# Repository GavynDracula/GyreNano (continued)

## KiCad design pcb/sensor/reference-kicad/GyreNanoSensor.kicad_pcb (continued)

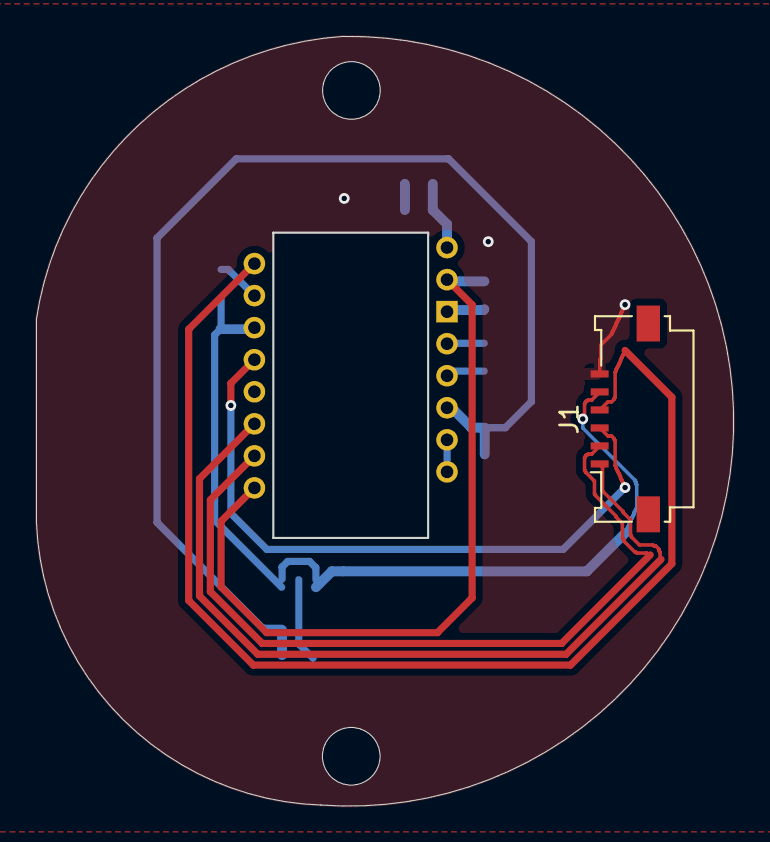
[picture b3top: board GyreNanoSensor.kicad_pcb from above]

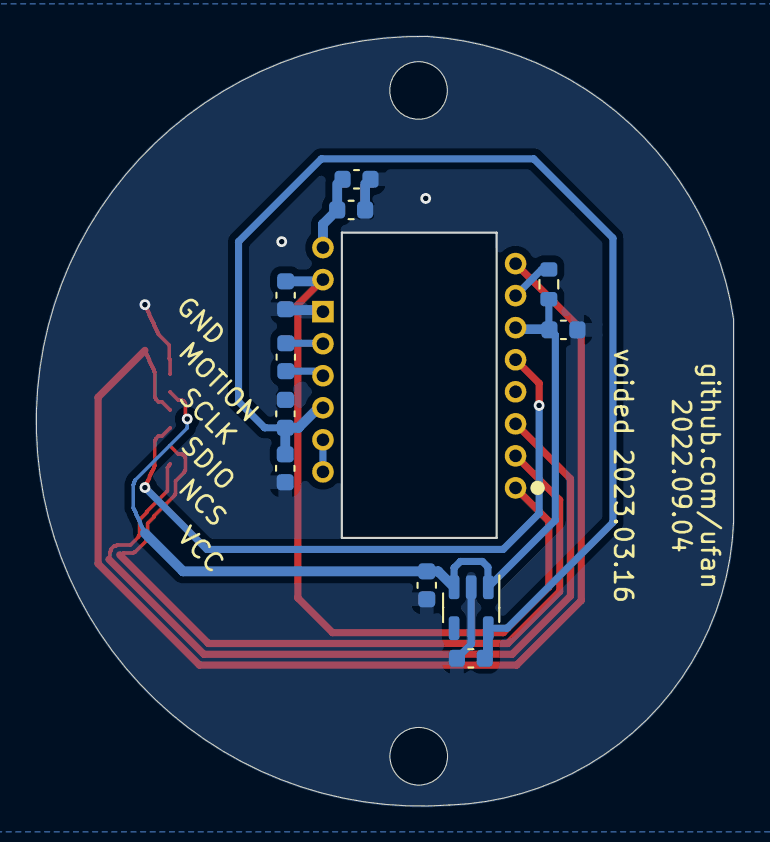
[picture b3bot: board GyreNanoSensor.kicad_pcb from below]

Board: 2 copper layers, 38.7 x 42.8 mm, 15 parts (12 on the bottom side), 13 nets.

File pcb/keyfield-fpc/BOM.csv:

采购类别,物料,型号或参数,封装规格,一套用量,建议备料数量,已有数量,还缺数量,说明
核心,MX热插拔座,Kailh CPG151101S11-16,MX socket,35,40,,,主列30+拇指5
核心,按键二极管,1N4148W-7-F,SOD-123,35,50或100,,,不得误买SOD-323
核心,FFC插座,Molex 2005280060,6P 1mm 下接触 卧贴,27,30,,,FPC12+holder14+sensor1；左J7可少装1；已焊件扣减
核心,电源开关,C&K JS102011SAQN,SPDT SMT,2,3,,,holder SW1
核心,电池板端插座,JST B2B-PH-SM4-TB,PH2.0 2P立式贴片,2,3,,,不是直插座
复用或采购,电池插头线,PHR-2配套线,PH2.0 2P,2,2或复用,,,板端1正2负；实测极性
待试装,FFC排线,6芯 1.00mm 插入端0.30±0.05mm,接点面及长度待定,13,先小样,,,12键区+1sensor；可试100/150/250mm同面异面各1，不是定长采购表
复用,主控,nrfmicro 1.4,现有模块,2,优先复用,,,替代主控需重新核对引脚电源和充电
待试装,主控排针,1x12 2.54mm,高度待确认,4,沿用或4条,,,可拔插还需4条匹配排母；未冻结堆叠
复用,轴体,现有MX兼容轴,MX,35,复用,,,
复用,键帽,现有键帽,匹配现用轴,35,复用,,,
复用,电池,现用电池,尺寸容量待记录,2,复用,,,
复用,球及光学组件,34mm球+原适配器镜片轴承,原组合,1,复用,,,
条件采购：新sensor,传感器,PMW3610,源板U2封装,1,1或复用,,,具体后缀和光学组合需核对；不买任意模块替代
条件采购：新sensor,LDO,TCR2EF19,SOT-25/SMV 1.9V,1,2,,,U1；不要混用1.8V版
条件采购：新sensor,电容 C1 C9,10nF X7R >=10V,0603/1608,2,10,,,采购候选参数；旧LCSC编号不用
条件采购：新sensor,电容 C2 C4 C6 C7,100nF X7R >=10V,0603/1608,4,10,,,C4本版100nF
条件采购：新sensor,电容 C3,3.3uF 16V X5R/X7R候选,0603/1608,1,10,,,核对有效容量和LDO要求
条件采购：新sensor,电容 C5,1uF X7R >=10V,0603/1608,1,10,,,
条件采购：新sensor,电容 C8,10uF X7R >=6.3V,0603/1608,1,10,,,具体MPN待选，核对直流偏压有效容量
条件采购：新sensor,电阻 R1,2Mohm 1%,0603/1608,1,10,,,
机械,无铜FR4背衬,0.40mm 按DXF,每键独立,35,做2套18件共36,,,右侧剩1件；可另备试验件
待验证,背衬胶,胶层预算0.05mm,型号未冻结,1,先小样,,,胶层耐热厚度和剥离未验证，不直接用厚泡棉胶
